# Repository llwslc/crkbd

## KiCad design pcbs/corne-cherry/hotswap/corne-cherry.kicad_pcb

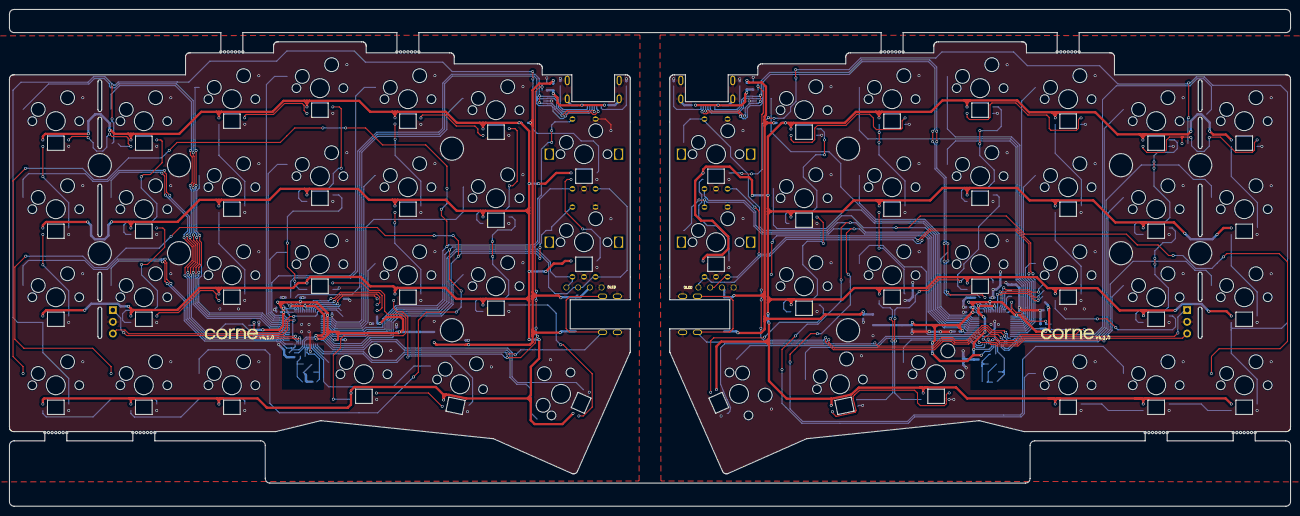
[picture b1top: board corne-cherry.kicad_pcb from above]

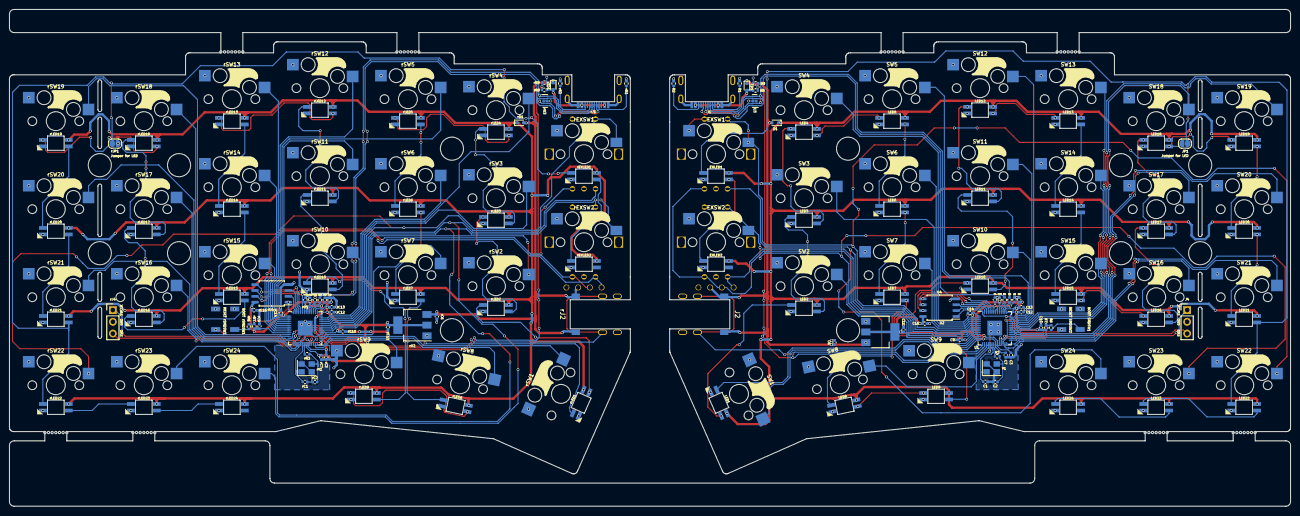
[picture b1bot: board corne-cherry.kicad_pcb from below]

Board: 2 copper layers, 277.2 x 107.5 mm, 190 parts (180 on the bottom side), 156 nets.

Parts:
BT1, BT2, BT3, BT4: Breakaway Tabs; Breakaway_Tabs
C1, C2: 27p; C_0402_1005Metric
C3, C4, C7, C9, C10, C12, C13, C14, C15: 100n; C_0402_1005Metric
C5, C8, C16: 1u; C_0402_1005Metric
C6, C11: 10u; C_0402_1005Metric
D1: 1N4148WT; D_SOD-523
EXLED1, EXLED2: YS-SK6812MINI-E
EXSW1, EXSW2: RotaryEncoder_Switch; keyswitch_cherrymx_hotswap_1u_rotary_encoder_ec12
J1: TYPE-C-31-M-13C
J2: TRS; PJ-398A-5A_PJ-399B-6A
J3: Conn_01x04; OLED
J4: Conn_01x03; PinHeader_1x03_P2.54mm_Vertical
JP1: SolderJumper_2_Bridged; SolderJumper-2_P1.3mm_Open_RoundedPad1.0x1.5mm
LED1, LED2, LED3, LED4, LED5, LED6, LED7, LED8, LED9, LED10, LED11, LED12, LED13, LED14, LED15, LED16, LED17, LED18, LED19, LED20, LED21, LED22, LED23, LED24: YS-SK6812MINI-E
R1, R2: 5.1k; R_0402_1005Metric
R3, R6: 1k; R_0402_1005Metric
R4, R5: 27; R_0402_1005Metric
R7: 10k; R_0402_1005Metric
R8: 5.6k; R_0402_1005Metric
R9: 10K; R_0402_1005Metric
SMDSW1, SMDSW2: TS-1088R-02026
SW1: SW_Push; keyswitch_cherrymx_hotswap_1.5u
SW2, SW3, SW4, SW5, SW6, SW7, SW8, SW9, SW10, SW11, SW12, SW13, SW14, SW15, SW16, SW17, SW18, SW19, SW20, SW21, SW22, SW23, SW24: SW_Push; keyswitch_cherrymx_hotswap_1u
U1: RP2040; QFN-56-1EP_7x7mm_P0.4mm_EP3.2x3.2mm
U2: NCP1117LPST33T3G; SOT-223-3_TabPin2
U3: TPD4E05U06DQAR; USON-10_2.5x1.0mm_P0.5mm
U4: W25Q128JVSIQ; SOIC-8_5.23x5.23mm_P1.27mm
Y1: 12MHz 18pF; Crystal_SMD_3225-4Pin_3.2x2.5mm
ZD1: RB521S30T1G; D_SOD-523
rBT1, rBT2, rBT3, rBT4: Breakaway Tabs; Breakaway_Tabs
rC1, rC2: 27p; C_0402_1005Metric
rC3, rC4, rC7, rC9, rC10, rC12, rC13, rC14, rC15: 100n; C_0402_1005Metric
rC5, rC8, rC16: 1u; C_0402_1005Metric
rC6, rC11: 10u; C_0402_1005Metric
rD1: 1N4148WT; D_SOD-523
rEXLED1, rEXLED2: YS-SK6812MINI-E
rEXSW1, rEXSW2: RotaryEncoder_Switch; keyswitch_cherrymx_hotswap_1u_rotary_encoder_ec12
rJ1: TYPE-C-31-M-13C
rJ2: TRS; PJ-398A-5A_PJ-399B-6A
rJ3: Conn_01x04; OLED
rJ4: Conn_01x03; PinHeader_1x03_P2.54mm_Vertical
rJP1: SolderJumper_2_Bridged; SolderJumper-2_P1.3mm_Open_RoundedPad1.0x1.5mm
rLED1, rLED2, rLED3, rLED4, rLED5, rLED6, rLED7, rLED8, rLED9, rLED10, rLED11, rLED12, rLED13, rLED14, rLED15, rLED16, rLED17, rLED18, rLED19, rLED20, rLED21, rLED22, rLED23, rLED24: YS-SK6812MINI-E
rR1, rR2: 5.1k; R_0402_1005Metric
rR3, rR6: 1k; R_0402_1005Metric
rR4, rR5: 27; R_0402_1005Metric
rR7: 10k; R_0402_1005Metric
rR8: 5.6k; R_0402_1005Metric
rR9: 10K; R_0402_1005Metric
rSMDSW1, rSMDSW2: TS-1088R-02026
rSW1: SW_Push; keyswitch_cherrymx_hotswap_1.5u
rSW2, rSW3, rSW4, rSW5, rSW6, rSW7, rSW8, rSW9, rSW10, rSW11, rSW12, rSW13, rSW14, rSW15, rSW16, rSW17, rSW18, rSW19, rSW20, rSW21, rSW22, rSW23, rSW24: SW_Push; keyswitch_cherrymx_hotswap_1u
rU1: RP2040; QFN-56-1EP_7x7mm_P0.4mm_EP3.2x3.2mm
rU2: NCP1117LPST33T3G; SOT-223-3_TabPin2
rU3: TPD4E05U06DQAR; USON-10_2.5x1.0mm_P0.5mm
rU4: W25Q128JVSIQ; SOIC-8_5.23x5.23mm_P1.27mm
rY1: 12MHz 18pF; Crystal_SMD_3225-4Pin_3.2x2.5mm
rZD1: RB521S30T1G; D_SOD-523

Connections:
+1V1: C3.1, C4.1, C5.1, U1.23 (DVDD), U1.45 (VREG_VOUT), U1.50 (DVDD)
+1V1R: rC3.1, rC4.1, rC5.1, rU1.23 (DVDD), rU1.45 (VREG_VOUT), rU1.50 (DVDD)
+3V3: C7.1, C8.1, C9.1, C10.1, C11.1, C12.1, C13.1, C14.1, C15.1, C16.1, R7.2, U1.1 (IOVDD), U1.10 (IOVDD), U1.22 (IOVDD), U1.32 (GPIO21), U1.33 (IOVDD), U1.42 (IOVDD), U1.43 (ADC_AVDD), U1.44 (VREG_IN), U1.48 (USB_VDD), U1.49 (IOVDD), U2.2 (VO), U4.8 (VCC)
+3V3R: rC7.1, rC8.1, rC9.1, rC10.1, rC11.1, rC12.1, rC13.1, rC14.1, rC15.1, rC16.1, rR7.2, rU1.1 (IOVDD), rU1.10 (IOVDD), rU1.22 (IOVDD), rU1.33 (IOVDD), rU1.42 (IOVDD), rU1.43 (ADC_AVDD), rU1.44 (VREG_IN), rU1.48 (USB_VDD), rU1.49 (IOVDD), rU2.2 (VO), rU4.8 (VCC)
+5V: C6.1, D1.2 (A), J2.T, J3.3, U2.3 (VI), ZD1.1 (K)
+5VR: rC6.1, rD1.2 (A), rJ2.T, rJ3.3, rU2.3 (VI), rZD1.1 (K)
/left/D+: J1.A6 (D+), J1.B6 (D+), R4.1, U3.1 (D1+), U3.4 (D2+), U3.7 (NC), U3.10 (NC)
/left/D-: J1.A7 (D-), J1.B7 (D-), R5.2, U3.2 (D1-), U3.5 (D2-), U3.6 (NC), U3.9 (NC)
/left/KEY1: SW1.1, U1.14 (GPIO11)
/left/KEY2: SW2.1, U1.12 (GPIO9)
/left/KEY3: SW3.1, U1.4 (GPIO2)
/left/KEY4: SW4.1, U1.2 (GPIO0)
/left/KEY5: SW5.1, U1.41 (GPIO29_ADC3)
/left/KEY6: SW6.1, U1.3 (GPIO1)
/left/KEY7: SW7.1, U1.5 (GPIO3)
/left/KEY8: SW8.1, U1.18 (GPIO15)
/left/KEY9: SW9.1, U1.17 (GPIO14)
/left/KEY10: SW10.1, U1.40 (GPIO28_ADC2)
/left/KEY11: SW11.1, U1.39 (GPIO27_ADC1)
/left/KEY12: SW12.1, U1.38 (GPIO26_ADC0)
/left/KEY13: SW13.1, U1.35 (GPIO23)
/left/KEY14: SW14.1, U1.36 (GPIO24)
/left/KEY15: SW15.1, U1.37 (GPIO25)
/left/KEY16: SW16.1, U1.27 (GPIO16)
/left/KEY17: SW17.1, U1.29 (GPIO18)
/left/KEY18: SW18.1, U1.31 (GPIO20)
/left/KEY19: SW19.1, U1.34 (GPIO22)
/left/KEY20: SW20.1, U1.30 (GPIO19)
/left/KEY21: SW21.1, U1.28 (GPIO17)
/left/KEY22: EXSW1.S2, SW22.1, U1.6 (GPIO4)
/left/KEY23: EXSW2.S2, SW23.1, U1.11 (GPIO8)
/left/KEY24: EXSW1.A, SW24.1, U1.7 (GPIO5)
/left/LED: LED1.4 (DIN), U1.13 (GPIO10)
/left/QSPI_SCLK: U1.52 (QSPI_SCLK), U4.6 (CLK)
/left/QSPI_SD0: U1.53 (QSPI_SD0), U4.5 (DI(IO0))
/left/QSPI_SD1: U1.55 (QSPI_SD1), U4.2 (DO(IO1))
/left/QSPI_SD2: U1.54 (QSPI_SD2), U4.3 (IO2)
/left/QSPI_SD3: U1.51 (QSPI_SD3), U4.7 (IO3)
/left/QSPI_SS: R6.1, R7.1, U1.56 (QSPI_SS), U4.1 (~CS)
/left/RE1A: EXSW2.A, J3.1, U1.8 (GPIO6)
/left/REB: EXSW1.B, EXSW2.B, J3.2, U1.9 (GPIO7)
/left/SWCLK: J4.1, U1.24 (SWCLK)
/left/SWD: J4.3, U1.25 (SWD)
/left/TX: J2.R, U1.15 (GPIO12)
/left/USB_VBUS_PIN: R8.2, R9.1, U1.16 (GPIO13)
/right/D+: rJ1.A6 (D+), rJ1.B6 (D+), rR4.1, rU3.1 (D1+), rU3.4 (D2+), rU3.7 (NC), rU3.10 (NC)
/right/D-: rJ1.A7 (D-), rJ1.B7 (D-), rR5.2, rU3.2 (D1-), rU3.5 (D2-), rU3.6 (NC), rU3.9 (NC)
/right/KEY1: rSW1.1, rU1.30 (GPIO19)
/right/KEY2: rSW2.1, rU1.34 (GPIO22)
/right/KEY3: rSW3.1, rU1.38 (GPIO26_ADC0)
/right/KEY4: rSW4.1, rU1.39 (GPIO27_ADC1)
/right/KEY5: rSW5.1, rU1.3 (GPIO1)
/right/KEY6: rSW6.1, rU1.40 (GPIO28_ADC2)
/right/KEY7: rSW7.1, rU1.31 (GPIO20)
/right/KEY8: rSW8.1, rU1.28 (GPIO17)
/right/KEY9: rSW9.1, rU1.27 (GPIO16)
/right/KEY10: rSW10.1, rU1.41 (GPIO29_ADC3)
/right/KEY11: rSW11.1, rU1.2 (GPIO0)
/right/KEY12: rSW12.1, rU1.4 (GPIO2)
/right/KEY13: rSW13.1, rU1.5 (GPIO3)
/right/KEY14: rSW14.1, rU1.6 (GPIO4)
/right/KEY15: rSW15.1, rU1.7 (GPIO5)
/right/KEY16: rSW16.1, rU1.29 (GPIO18)
/right/KEY17: rSW17.1, rU1.17 (GPIO14)
/right/KEY18: rSW18.1, rU1.12 (GPIO9)
/right/KEY19: rSW19.1, rU1.11 (GPIO8)
/right/KEY20: rSW20.1, rU1.14 (GPIO11)
/right/KEY21: rSW21.1, rU1.18 (GPIO15)
/right/KEY22: rEXSW1.S2, rSW22.1, rU1.37 (GPIO25)
/right/KEY23: rEXSW2.S2, rSW23.1, rU1.35 (GPIO23)
/right/KEY24: rEXSW1.A, rSW24.1, rU1.36 (GPIO24)
/right/LED: rLED1.4 (DIN), rU1.13 (GPIO10)
/right/QSPI_SCLK: rU1.52 (QSPI_SCLK), rU4.6 (CLK)
/right/QSPI_SD0: rU1.53 (QSPI_SD0), rU4.5 (DI(IO0))
/right/QSPI_SD1: rU1.55 (QSPI_SD1), rU4.2 (DO(IO1))
/right/QSPI_SD2: rU1.54 (QSPI_SD2), rU4.3 (IO2)
/right/QSPI_SD3: rU1.51 (QSPI_SD3), rU4.7 (IO3)
/right/QSPI_SS: rR6.1, rR7.1, rU1.56 (QSPI_SS), rU4.1 (~CS)
/right/RE1A: rEXSW2.A, rJ3.1, rU1.8 (GPIO6)
/right/REB: rEXSW1.B, rEXSW2.B, rJ3.2, rU1.9 (GPIO7)
/right/SWCLK: rJ4.1, rU1.24 (SWCLK)
/right/SWD: rJ4.3, rU1.25 (SWD)
/right/TX: rJ2.R, rU1.15 (GPIO12)
/right/USB_VBUS_PIN: rR8.2, rR9.1, rU1.16 (GPIO13)
GND: C1.2, C2.2, C3.2, C4.2, C5.2, C6.2, C7.2, C8.2, C9.2, C10.2, C11.2, C12.2, C13.2, C14.2, C15.2, C16.2, EXLED1.3 (VSS), EXLED2.3 (VSS), EXSW1.C, EXSW1.S1, EXSW2.C, EXSW2.S1, J1.A1 (GND), J1.A12 (GND), J1.B1 (GND), J1.B12 (GND), J1.S1 (SHIELD), J2.S, J3.4, J4.2, LED1.3 (VSS), LED2.3 (VSS), LED3.3 (VSS), LED4.3 (VSS), LED5.3 (VSS), LED6.3 (VSS), LED7.3 (VSS), LED8.3 (VSS), LED9.3 (VSS), LED10.3 (VSS), LED11.3 (VSS), LED12.3 (VSS), LED13.3 (VSS), LED14.3 (VSS), LED15.3 (VSS), LED16.3 (VSS), LED17.3 (VSS), LED18.3 (VSS), LED19.3 (VSS), LED20.3 (VSS), LED21.3 (VSS), LED22.3 (VSS), LED23.3 (VSS), LED24.3 (VSS), R1.1, R2.1, R9.2, SMDSW1.1, SMDSW2.1, SW1.2, SW2.2, SW3.2, SW4.2, SW5.2, SW6.2, SW7.2, SW8.2, SW9.2, SW10.2, SW11.2, SW12.2, SW13.2, SW14.2, SW15.2, SW16.2, SW17.2, SW18.2, SW19.2, SW20.2, SW21.2, SW22.2, SW23.2, SW24.2, U1.19 (TESTEN), U1.57 (GND), U2.1 (GND), U3.3 (GND), U3.8 (GND), U4.4 (GND), Y1.2, Y1.4
GNDR: rC1.2, rC2.2, rC3.2, rC4.2, rC5.2, rC6.2, rC7.2, rC8.2, rC9.2, rC10.2, rC11.2, rC12.2, rC13.2, rC14.2, rC15.2, rC16.2, rEXLED1.3 (VSS), rEXLED2.3 (VSS), rEXSW1.C, rEXSW1.S1, rEXSW2.C, rEXSW2.S1, rJ1.A1 (GND), rJ1.A12 (GND), rJ1.B1 (GND), rJ1.B12 (GND), rJ1.S1 (SHIELD), rJ2.S, rJ3.4, rJ4.2, rLED1.3 (VSS), rLED2.3 (VSS), rLED3.3 (VSS), rLED4.3 (VSS), rLED5.3 (VSS), rLED6.3 (VSS), rLED7.3 (VSS), rLED8.3 (VSS), rLED9.3 (VSS), rLED10.3 (VSS), rLED11.3 (VSS), rLED12.3 (VSS), rLED13.3 (VSS), rLED14.3 (VSS), rLED15.3 (VSS), rLED16.3 (VSS), rLED17.3 (VSS), rLED18.3 (VSS), rLED19.3 (VSS), rLED20.3 (VSS), rLED21.3 (VSS), rLED22.3 (VSS), rLED23.3 (VSS), rLED24.3 (VSS), rR1.1, rR2.1, rR9.2, rSMDSW1.1, rSMDSW2.1, rSW1.2, rSW2.2, rSW3.2, rSW4.2, rSW5.2, rSW6.2, rSW7.2, rSW8.2, rSW9.2, rSW10.2, rSW11.2, rSW12.2, rSW13.2, rSW14.2, rSW15.2, rSW16.2, rSW17.2, rSW18.2, rSW19.2, rSW20.2, rSW21.2, rSW22.2, rSW23.2, rSW24.2, rU1.19 (TESTEN), rU1.32 (GPIO21), rU1.57 (GND), rU2.1 (GND), rU3.3 (GND), rU3.8 (GND), rU4.4 (GND), rY1.2, rY1.4
unnamed: C2.1, R3.1, Y1.3
unnamed: D1.1 (K), EXLED1.1 (VDD), EXLED2.1 (VDD), LED1.1 (VDD), LED2.1 (VDD), LED3.1 (VDD), LED4.1 (VDD), LED5.1 (VDD), LED6.1 (VDD), LED7.1 (VDD), LED8.1 (VDD), LED9.1 (VDD), LED10.1 (VDD), LED11.1 (VDD), LED12.1 (VDD), LED13.1 (VDD), LED14.1 (VDD), LED15.1 (VDD), LED16.1 (VDD), LED17.1 (VDD), LED18.1 (VDD), LED19.1 (VDD), LED20.1 (VDD), LED21.1 (VDD), LED22.1 (VDD), LED23.1 (VDD), LED24.1 (VDD)
unnamed: EXLED1.4 (DIN), JP1.2 (B), LED21.2 (DOUT), LED22.4 (DIN)
unnamed: EXLED1.2 (DOUT), EXLED2.4 (DIN)
unnamed: J1.A5 (CC1), R1.2
unnamed: J1.B5 (CC2), R2.2
unnamed: JP1.1 (A), LED18.2 (DOUT), LED19.4 (DIN)
unnamed: LED1.2 (DOUT), LED2.4 (DIN)
unnamed: LED2.2 (DOUT), LED3.4 (DIN)
unnamed: LED3.2 (DOUT), LED4.4 (DIN)
unnamed: LED4.2 (DOUT), LED5.4 (DIN)
unnamed: LED5.2 (DOUT), LED6.4 (DIN)
unnamed: LED6.2 (DOUT), LED7.4 (DIN)
unnamed: LED7.2 (DOUT), LED8.4 (DIN)
unnamed: LED8.2 (DOUT), LED9.4 (DIN)
unnamed: LED9.2 (DOUT), LED10.4 (DIN)
unnamed: LED10.2 (DOUT), LED11.4 (DIN)
unnamed: LED11.2 (DOUT), LED12.4 (DIN)
unnamed: LED12.2 (DOUT), LED13.4 (DIN)
unnamed: LED13.2 (DOUT), LED14.4 (DIN)
unnamed: LED14.2 (DOUT), LED15.4 (DIN)
unnamed: LED15.2 (DOUT), LED16.4 (DIN)
unnamed: LED16.2 (DOUT), LED17.4 (DIN)
unnamed: LED17.2 (DOUT), LED18.4 (DIN)
unnamed: LED19.2 (DOUT), LED20.4 (DIN)
unnamed: LED20.2 (DOUT), LED21.4 (DIN)
unnamed: LED22.2 (DOUT), LED23.4 (DIN)
unnamed: LED23.2 (DOUT), LED24.4 (DIN)
unnamed: R6.2, SMDSW1.2
unnamed: SMDSW2.2, U1.26 (RUN)
unnamed: R5.1, U1.46 (USB_DM)
unnamed: R4.2, U1.47 (USB_DP)
unnamed: C1.1, U1.20 (XIN), Y1.1
unnamed: R3.2, U1.21 (XOUT)
unnamed: rC2.1, rR3.1, rY1.3
unnamed: rD1.1 (K), rEXLED1.1 (VDD), rEXLED2.1 (VDD), rLED1.1 (VDD), rLED2.1 (VDD), rLED3.1 (VDD), rLED4.1 (VDD), rLED5.1 (VDD), rLED6.1 (VDD), rLED7.1 (VDD), rLED8.1 (VDD), rLED9.1 (VDD), rLED10.1 (VDD), rLED11.1 (VDD), rLED12.1 (VDD), rLED13.1 (VDD), rLED14.1 (VDD), rLED15.1 (VDD), rLED16.1 (VDD), rLED17.1 (VDD), rLED18.1 (VDD), rLED19.1 (VDD), rLED20.1 (VDD), rLED21.1 (VDD), rLED22.1 (VDD), rLED23.1 (VDD), rLED24.1 (VDD)
unnamed: rEXLED1.4 (DIN), rJP1.2 (B), rLED21.2 (DOUT), rLED22.4 (DIN)
unnamed: rEXLED1.2 (DOUT), rEXLED2.4 (DIN)
unnamed: rJ1.A5 (CC1), rR1.2
unnamed: rJ1.B5 (CC2), rR2.2
unnamed: rJP1.1 (A), rLED18.2 (DOUT), rLED19.4 (DIN)
unnamed: rLED1.2 (DOUT), rLED2.4 (DIN)
unnamed: rLED2.2 (DOUT), rLED3.4 (DIN)
unnamed: rLED3.2 (DOUT), rLED4.4 (DIN)
unnamed: rLED4.2 (DOUT), rLED5.4 (DIN)
unnamed: rLED5.2 (DOUT), rLED6.4 (DIN)
unnamed: rLED6.2 (DOUT), rLED7.4 (DIN)
unnamed: rLED7.2 (DOUT), rLED8.4 (DIN)
unnamed: rLED8.2 (DOUT), rLED9.4 (DIN)
unnamed: rLED9.2 (DOUT), rLED10.4 (DIN)
unnamed: rLED10.2 (DOUT), rLED11.4 (DIN)
unnamed: rLED11.2 (DOUT), rLED12.4 (DIN)
unnamed: rLED12.2 (DOUT), rLED13.4 (DIN)
unnamed: rLED13.2 (DOUT), rLED14.4 (DIN)
unnamed: rLED14.2 (DOUT), rLED15.4 (DIN)
unnamed: rLED15.2 (DOUT), rLED16.4 (DIN)
unnamed: rLED16.2 (DOUT), rLED17.4 (DIN)
unnamed: rLED17.2 (DOUT), rLED18.4 (DIN)
unnamed: rLED19.2 (DOUT), rLED20.4 (DIN)
unnamed: rLED20.2 (DOUT), rLED21.4 (DIN)
unnamed: rLED22.2 (DOUT), rLED23.4 (DIN)
unnamed: rLED23.2 (DOUT), rLED24.4 (DIN)
unnamed: rR6.2, rSMDSW1.2
unnamed: rSMDSW2.2, rU1.26 (RUN)
unnamed: rR5.1, rU1.46 (USB_DM)
unnamed: rR4.2, rU1.47 (USB_DP)
unnamed: rC1.1, rU1.20 (XIN), rY1.1
unnamed: rR3.2, rU1.21 (XOUT)
VBUS: J1.A4 (VBUS), J1.A9 (VBUS), J1.B4 (VBUS), J1.B9 (VBUS), R8.1, ZD1.2 (A)
VBUSR: rJ1.A4 (VBUS), rJ1.A9 (VBUS), rJ1.B4 (VBUS), rJ1.B9 (VBUS), rR8.1, rZD1.2 (A)

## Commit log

2025-07-11 upgrade KiCad project to version 9.0
2025-07-14 KiCad v9
2025-07-14 add keys and LEDs
2025-07-15 update project settings
2025-07-15 add LEDs wiring
2025-07-15 add left keys wiring
2025-07-16 modify PCB edge
2025-07-16 add right keys wiring
2025-07-17 named
2025-07-17 logo
2025-07-18 plate
2025-07-18 update project plot setting
2025-07-18 update plate
2025-07-19 update plate plot settting
2025-08-08 update init shell
2025-08-09 fork corne rev4_1
2025-08-10 rev1
2025-08-11 fixed left LED5 wiring issue
2025-08-14 remove the boot button cutout
2025-08-26 update 3d model
2025-08-28 board thickness
2025-09-05 update logo
2025-09-05 update oled timeout
2025-09-05 update oled status
2025-09-09 SPLIT_OLED_ENABLE
